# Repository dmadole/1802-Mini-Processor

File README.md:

# 1802-Mini-Processor
This is the 1802 processor card for the [1802/Mini](https://github.com/dmadole/1802-Mini) system. It supports the following features:

* CDP1802, CDP1804 (A only), CDP1805, or CDP1806 processors
* 64K of memory in two 32K RAM, EPROM, or EEPROM devices
* Supports 62C64, 62C256, 27C64, 27C256, 28C64, 28C256
* Can temporarily map a ROM at $8000 to $0000 at reset
* Eight  indicator LEDS with selectable polarity for each
* TTL level port with Q and selectable EF pin for soft serial
* Transmit and receive polarity selectable on serial port
* Designed for 4 Mhz but can run 8Mhz with suitable processor
* Stable power-on reset circuit is jumper-selectable
* Convenient mini-USB connector for 5 volt power input
* Form factor allows stacking or backplane by connector choice
* Can run totally standalone or expanded with additional cards
* Configurable to be able to run most "Classic Elf" software
* Highly annoted silkscreen documents most settings and pins

Gerber files for the PCBs and PDF schematics can be found in [Releases](https://github.com/dmadole/1802-Mini-Processor/releases).

BOMS and any applicable errata or other notes can be found in [notes](https://github.com/dmadole/1802-Mini-Processor/tree/main/notes).

For availability of kits and bare PCBs please see http://madole.net/1802/mini/kits

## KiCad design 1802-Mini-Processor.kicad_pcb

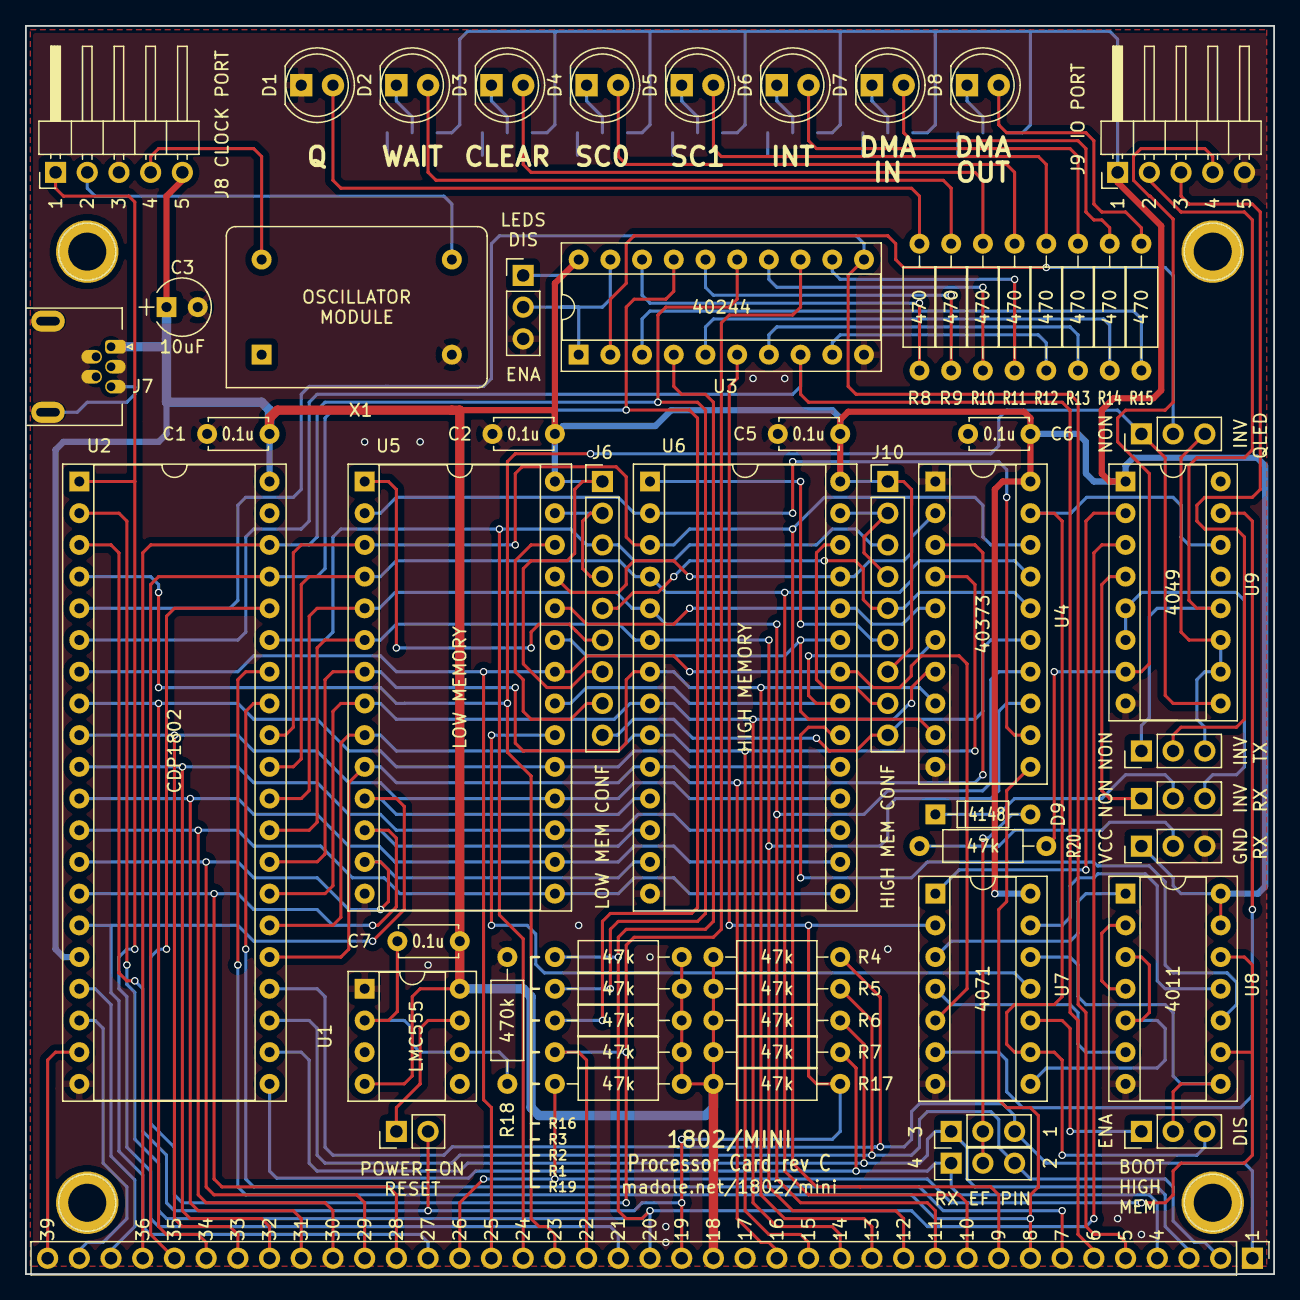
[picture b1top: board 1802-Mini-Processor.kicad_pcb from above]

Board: 2 copper layers, 100.0 x 100.0 mm, 71 parts (0 on the bottom side), 102 nets.

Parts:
C1, C2, C5, C6, C7: 0.1u; C_Disc_D4.7mm_W2.5mm_P5.00mm
C3: 10uF; CP_Radial_Tantal_D4.5mm_P2.50mm
D1, D2, D3, D4, D5, D6, D7, D8: LED_Small; LED_D5.0mm
D9: 4148; D_DO-35_SOD27_P7.62mm_Horizontal
J1, J2, J3, J4: Mount; 1pin
J5: Expansion; Pin_Header_Straight_1x39_Pitch2.54mm
J6: SLOT_1_CONFIG; Pin_Header_Straight_1x09_Pitch2.54mm
J7: 56579-0519; USB_Mini-AB_Molex_56579_0519
J8: ClockPort; Pin_Header_Angled_1x05_Pitch2.54mm
J9: Q_Connector; Pin_Header_Angled_1x05_Pitch2.54mm
J10: SLOT_2_CONFIG; Pin_Header_Straight_1x09_Pitch2.54mm
JP1: POR; Pin_Header_Straight_1x02_Pitch2.54mm
JP3: WAIT; SolderJumper-3_P2.0mm_Open_TrianglePad1.0x1.5mm_NumberLabels
JP4: CLEAR; SolderJumper-3_P2.0mm_Open_TrianglePad1.0x1.5mm_NumberLabels
JP5: SC0; SolderJumper-3_P2.0mm_Open_TrianglePad1.0x1.5mm_NumberLabels
JP6: SC1; SolderJumper-3_P2.0mm_Open_TrianglePad1.0x1.5mm_NumberLabels
JP7: INT; SolderJumper-3_P2.0mm_Open_TrianglePad1.0x1.5mm_NumberLabels
JP8: TX_INV; Pin_Header_Straight_1x03_Pitch2.54mm
JP9, JP16: RX_SEL; Pin_Header_Straight_1x03_Pitch2.54mm
JP10: RX_INV; Pin_Header_Straight_1x03_Pitch2.54mm
JP11: RX_IDL; Pin_Header_Straight_1x03_Pitch2.54mm
JP12: BM_OE; Pin_Header_Straight_1x03_Pitch2.54mm
JP13: SLOT2_MIR; Pin_Header_Straight_1x03_Pitch2.54mm
JP14: DMAIN; SolderJumper-3_P2.0mm_Open_TrianglePad1.0x1.5mm_NumberLabels
JP15: DMAOUT; SolderJumper-3_P2.0mm_Open_TrianglePad1.0x1.5mm_NumberLabels
JP17: Q_LED; Pin_Header_Straight_1x03_Pitch2.54mm
R1, R2, R3, R4, R5, R6, R7, R16, R17, R19, R20: 47k; R_Axial_DIN0207_L6.3mm_D2.5mm_P10.16mm_Horizontal
R8, R9, R10, R11, R12, R13, R14, R15: 470; R_Axial_DIN0207_L6.3mm_D2.5mm_P10.16mm_Horizontal
R18: 470k; R_Axial_DIN0207_L6.3mm_D2.5mm_P10.16mm_Horizontal
U1: LMC555; DIP-8_W7.62mm_Socket
U2: CDP1802; DIP-40_W15.24mm_Socket
U3: 40244; DIP-20_W7.62mm_Socket
U4: 40373; DIP-20_W7.62mm_Socket
U5: LO_MEM; DIP-28_W15.24mm_Socket
U6: HI_MEM; DIP-28_W15.24mm_Socket
U7: 4071; DIP-14_W7.62mm_Socket
U8: 4011; DIP-14_W7.62mm_Socket
U9: 4049; DIP-16_W7.62mm_Socket
X1: CXO-DIP14; Oscillator_DIP-14

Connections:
/BUS0: J5.27, U2.15, U5.11, U6.11
/BUS1: J5.28, U2.14, U5.12, U6.12
/BUS2: J5.29, U2.13, U5.13, U6.13
/BUS3: J5.30, U2.12, U5.15, U6.15
/BUS4: J5.31, U2.11, U5.16, U6.16
/BUS5: J5.32, U2.10, U5.17, U6.17
/BUS6: J5.33, U2.9, U5.18, U6.18
/BUS7: J5.34, U2.8, U5.19, U6.19
/CLK_PWR: J8.4, X1.14
/MA0: J5.16, U2.25, U4.3, U5.10, U6.10
/MA1: J5.15, U2.26, U4.4, U5.9, U6.9
/MA2: J5.14, U2.27, U4.7, U5.8, U6.8
/MA3: J5.13, U2.28, U4.8, U5.7, U6.7
/MA4: J5.12, U2.29, U4.13, U5.6, U6.6
/MA5: J5.11, U2.30, U4.14, U5.5, U6.5
/MA6: J5.10, U2.31, U4.17, U5.4, U6.4
/MA7: J5.9, U2.32, U4.18, U5.3, U6.3
/MA8: U4.2, U5.25, U6.25
/MA9: U4.5, U5.24, U6.24
/MA10: U4.6, U5.21, U6.21
/MA11: U4.9, U5.23, U6.23
/MA12: U4.12, U5.2, U6.2
/MA13: J6.9, J10.9, U4.15
/MA14: J6.5, J10.5, U4.16
CLOCK: J5.21, J8.1, U2.1
DMA_IN: J5.36, R3.1, U2.38, U3.15
DMA_OUT: J5.35, R2.1, U2.37, U3.17
EF1: J5.1, JP9.3, R4.1, U2.24
EF2: J5.2, JP16.3, R5.1, U2.23
EF3: J5.3, JP9.1, R6.1, U2.22
EF4: J5.4, JP16.1, R7.1, U2.21
GND: C1.2, C2.2, C3.2, C5.2, C6.2, D1.1, J5.17, J7.5, J7.6, J8.3, J9.5, JP3.3, JP4.3, JP5.3, JP6.3, JP7.3, JP11.3, JP12.3, JP14.3, JP15.3, R18.1, U1.1, U2.20, U3.10, U4.1, U4.10, U5.14, U6.14, U7.7, U8.7, U9.8, X1.7
INTERRUPT: J5.22, R1.1, U2.36, U3.13
MA15: JP13.3, U4.19, U7.9, U9.14
MEN: J5.26, R19.1, U8.9, U8.12
MRD: J5.25, U2.7, U5.22, U6.22, U7.5
MWR: J5.24, J6.3, J10.3, U2.35
N0: J5.39, U2.19
N1: J5.38, U2.18
N2: J5.37, U2.17
unnamed: C7.2, R18.2, U1.2, U1.6
unnamed: D1.2, R8.2
unnamed: D2.1, JP3.2
unnamed: D2.2, R9.2
unnamed: D3.1, JP4.2
unnamed: D3.2, R10.2
unnamed: D4.1, JP5.2
unnamed: D4.2, R11.2
unnamed: D5.1, JP6.2
unnamed: D5.2, R12.2
unnamed: D6.1, JP7.2
unnamed: D6.2, R13.2
unnamed: D7.1, JP14.2
unnamed: D7.2, R14.2
unnamed: D8.1, JP15.2
unnamed: D8.2, R15.2
unnamed: D9.1, JP10.2
unnamed: D9.2, JP9.2, JP16.2
unnamed: J6.2, J6.4, U5.27
unnamed: J6.6, U5.1
unnamed: J6.8, U5.26
unnamed: J8.2, X1.8
unnamed: J9.2, JP8.1, U9.12
unnamed: J9.3, JP8.2
unnamed: J9.4, R20.2, U9.7
unnamed: J10.2, J10.4, U6.27
unnamed: J10.6, U6.1
unnamed: J10.8, U6.26
unnamed: JP1.1, U1.7
unnamed: JP10.1, U9.4
unnamed: JP10.3, U9.5, U9.6
unnamed: JP11.2, R20.1
unnamed: JP12.2, U3.1, U3.19
unnamed: JP13.1, U7.10
unnamed: JP13.2, U7.12, U8.8
unnamed: JP17.2, U3.2
unnamed: R8.1, U3.18
unnamed: R9.1, U3.16
unnamed: R10.1, U3.14
unnamed: R11.1, U3.12
unnamed: R12.1, U3.9
unnamed: R13.1, U3.7
unnamed: R14.1, U3.5
unnamed: R15.1, U3.3
unnamed: U7.1, U9.2
unnamed: U7.3, U8.1
unnamed: U7.4, U8.6
unnamed: U7.6, U9.15
unnamed: U7.8, U8.3, U8.5
unnamed: U7.13, U8.11
unnamed: U8.2, U8.4
Q: J5.23, JP17.1, U2.4, U9.9
SC0: J5.6, U2.6, U3.8
SC1: J5.5, U2.5, U3.11
SLOT1_CS: U5.20, U7.11
SLOT2_CS: U6.20, U8.10
TPA: J5.8, U2.34, U4.11
TPB: J5.7, U2.33
VCC: C1.1, C2.1, C3.1, C5.1, C6.1, C7.1, J5.18, J6.1, J6.7, J7.1, J8.5, J9.1, J10.1, J10.7, JP3.1, JP4.1, JP5.1, JP6.1, JP7.1, JP11.1, JP12.1, JP14.1, JP15.1, R1.2, R2.2, R3.2, R4.2, R5.2, R6.2, R7.2, R16.2, R17.2, R19.2, U1.4, U1.8, U2.16, U2.40, U3.20, U4.20, U5.28, U6.28, U7.14, U8.13, U8.14, U9.1
~CLEAR: J5.19, JP1.2, R17.1, U2.3, U3.6, U7.2
~Q: JP8.3, JP17.3, U9.10, U9.11
~WAIT: J5.20, R16.1, U2.2, U3.4, U9.3

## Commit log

2021-06-23 Initial upload
2021-06-23 Add BOM
2021-06-27 Added notes and reference numbers to BOM
2021-06-28 Correct mfr part no of single row header
2021-08-02 Rename to correct revision
2021-08-05 Update 1802-Mini-Processor-Build-Notes.md
    Added note about LED series resistor values
